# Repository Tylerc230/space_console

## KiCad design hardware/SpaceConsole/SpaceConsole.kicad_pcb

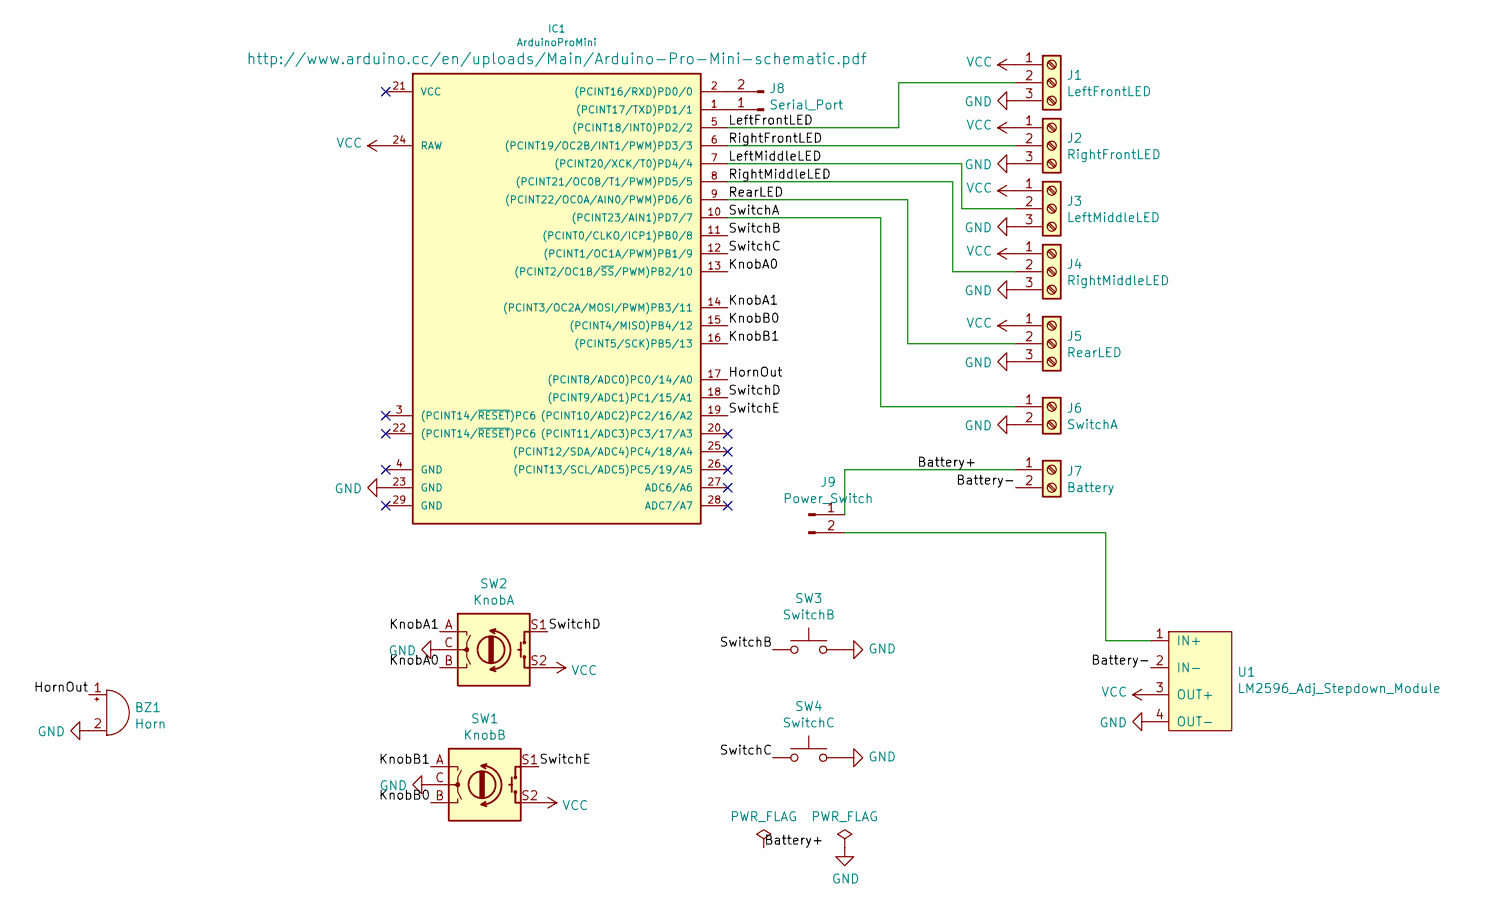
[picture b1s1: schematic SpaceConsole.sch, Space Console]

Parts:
BZ1: Horn; Buzzer_TDK_PS1240P02BT_D12.2mm_H6.5mm
IC1: ArduinoProMini; pro_mini
J1: LeftFrontLED; TerminalBlock_RND_205-00046_1x03_P5.00mm_Horizontal
J2: RightFrontLED; TerminalBlock_RND_205-00046_1x03_P5.00mm_Horizontal
J3: LeftMiddleLED; TerminalBlock_RND_205-00046_1x03_P5.00mm_Horizontal
J4: RightMiddleLED; TerminalBlock_RND_205-00046_1x03_P5.00mm_Horizontal
J5: RearLED; TerminalBlock_RND_205-00046_1x03_P5.00mm_Horizontal
J6: SwitchA; TerminalBlock_RND_205-00045_1x02_P5.00mm_Horizontal
J7: Battery; TerminalBlock_RND_205-00045_1x02_P5.00mm_Horizontal
J8: Serial_Port; PinHeader_1x02_P2.54mm_Vertical
J9: Power_Switch; PinHeader_1x02_P2.54mm_Vertical
SW1: KnobB; PinHeader_1x05_P2.54mm_Vertical
SW2: KnobA; PinHeader_1x05_P2.54mm_Vertical
SW3: SwitchB; PinHeader_1x02_P2.54mm_Vertical
SW4: SwitchC; PinHeader_1x02_P2.54mm_Vertical
U1: LM2596_Adj_Stepdown_Module

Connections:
/Battery+: J7.1, J9.1
/Battery-: J7.2, U1.2 (IN-)
/HornOut: BZ1.1 (-), IC1.17 ((PCINT8/ADC0)PC0/14/A0)
/KnobA0: IC1.13 ((PCINT2/OC1B/~SS~/PWM)PB2/10), SW2.B
/KnobA1: IC1.14 ((PCINT3/OC2A/MOSI/PWM)PB3/11), SW2.A
/KnobB0: IC1.15 ((PCINT4/MISO)PB4/12), SW1.B
/KnobB1: IC1.16 ((PCINT5/SCK)PB5/13), SW1.A
/LeftFrontLED: IC1.5 ((PCINT18/INT0)PD2/2), J1.2
/LeftMiddleLED: IC1.7 ((PCINT20/XCK/T0)PD4/4), J3.2
/RearLED: IC1.9 ((PCINT22/OC0A/AIN0/PWM)PD6/6), J5.2
/RightFrontLED: IC1.6 ((PCINT19/OC2B/INT1/PWM)PD3/3), J2.2
/RightMiddleLED: IC1.8 ((PCINT21/OC0B/T1/PWM)PD5/5), J4.2
/SwitchA: IC1.10 ((PCINT23/AIN1)PD7/7), J6.1
/SwitchB: IC1.11 ((PCINT0/CLKO/ICP1)PB0/8), SW3.1
/SwitchC: IC1.12 ((PCINT1/OC1A/PWM)PB1/9), SW4.1
/SwitchD: IC1.18 ((PCINT9/ADC1)PC1/15/A1), SW2.S1
/SwitchE: IC1.19 ((PCINT10/ADC2)PC2/16/A2), SW1.S1
GND: BZ1.2 (+), IC1.23 (GND), J1.3, J2.3, J3.3, J4.3, J5.3, J6.2, SW1.C, SW2.C, SW3.2, SW4.2, U1.4 (OUT-)
unnamed: IC1.1 ((PCINT17/TXD)PD1/1), J8.1
unnamed: IC1.2 ((PCINT16/RXD)PD0/0), J8.2
unnamed: J9.2, U1.1 (IN+)
VCC: IC1.24 (RAW), J1.1, J2.1, J3.1, J4.1, J5.1, SW1.S2, SW2.S2, U1.3 (OUT+)

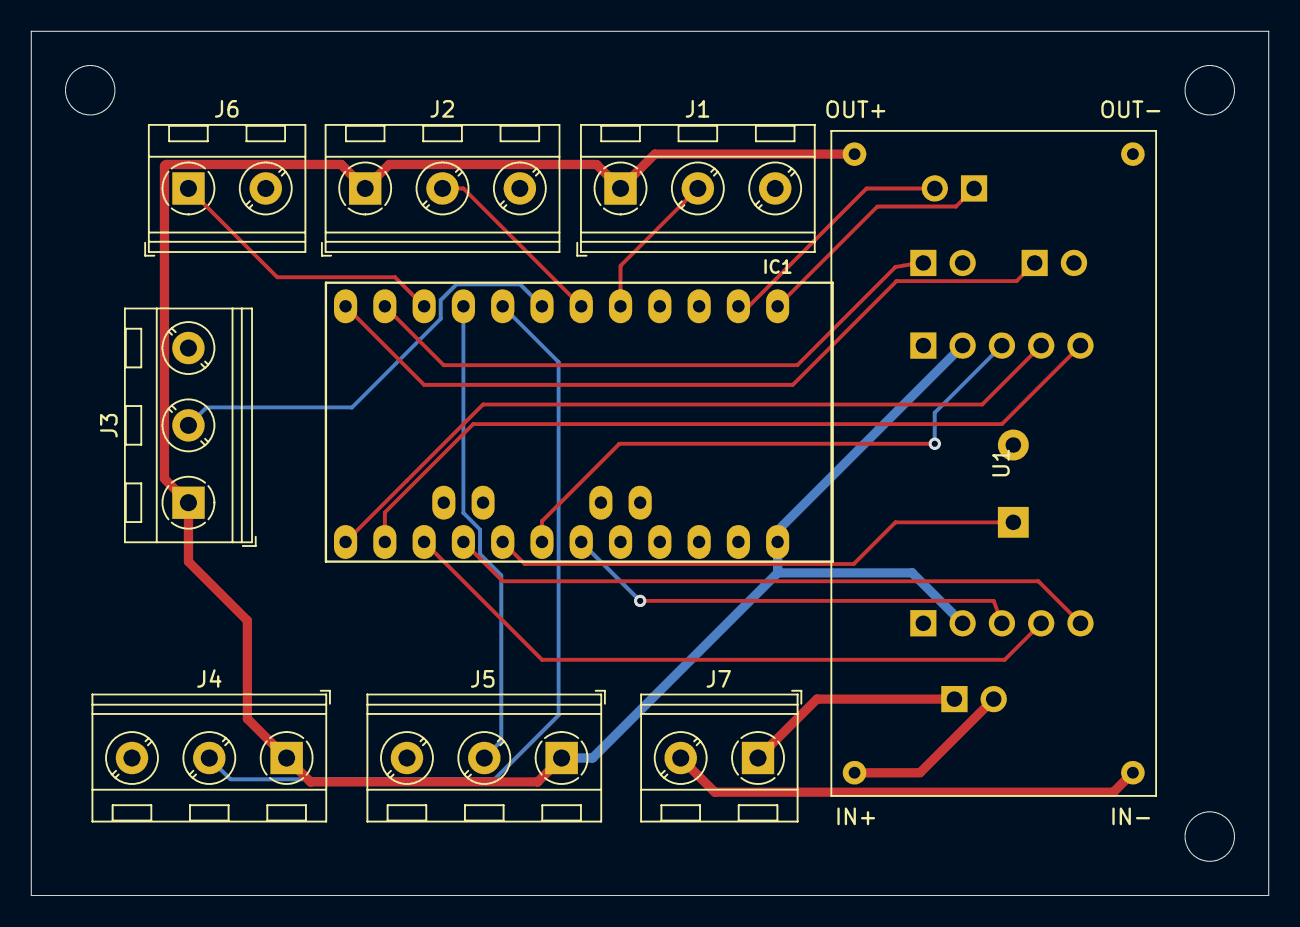
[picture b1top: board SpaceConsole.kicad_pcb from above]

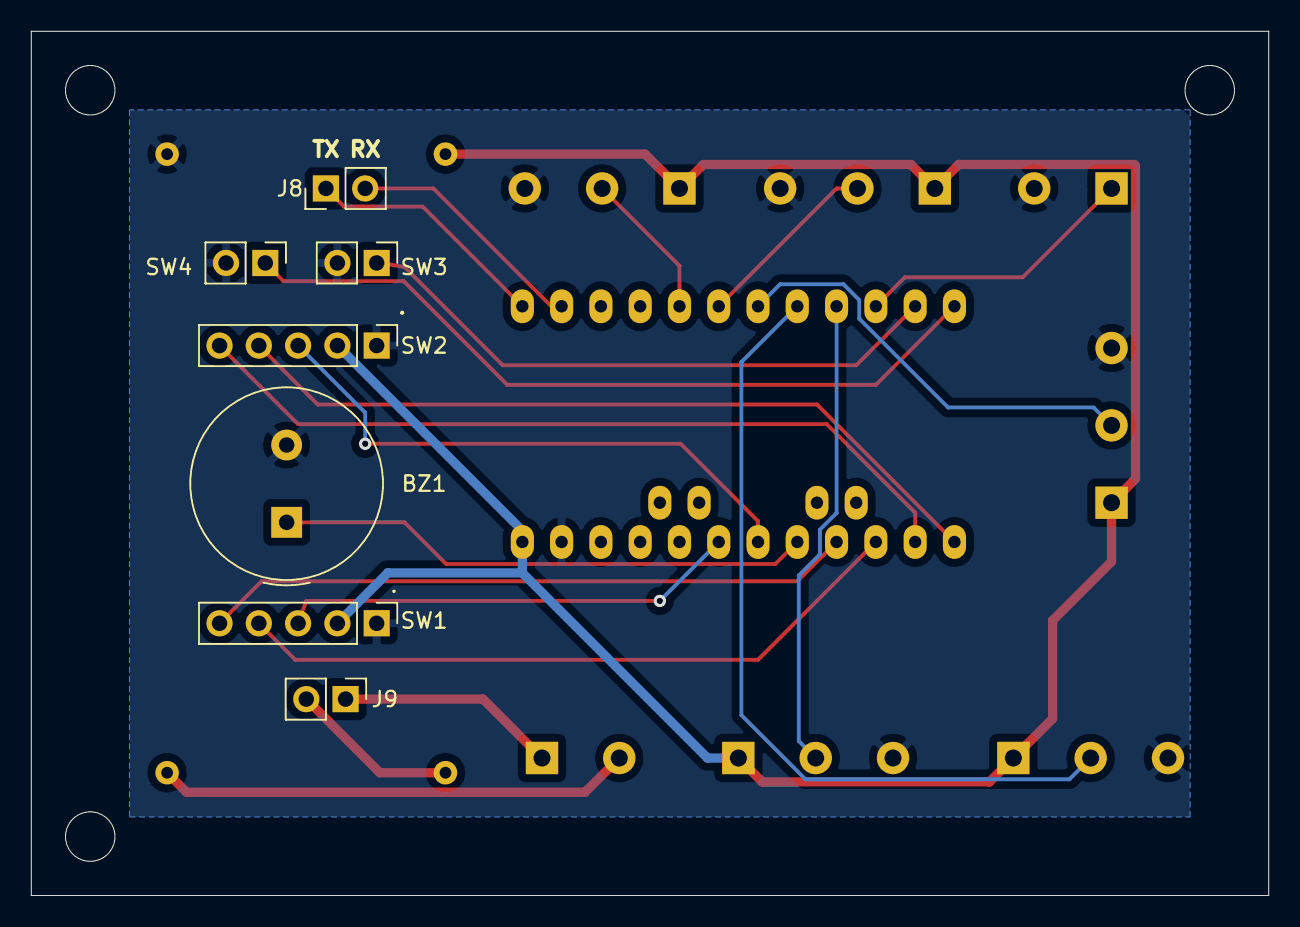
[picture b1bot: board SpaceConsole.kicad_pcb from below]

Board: 2 copper layers, 80.0 x 55.9 mm, 16 parts (7 on the bottom side), 22 nets.

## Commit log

2020-11-18 Initial commit with hardware stuff
2020-11-18 Add pro mini to schematic
2020-11-18 Label all pins
2020-11-18 Add screw terminals
2020-11-18 Add switching regulator and lib
2020-11-18 Add Know/switch headers
2020-11-18 Add footprints for all components (except Buck)
2020-11-18 Add footprint to Buck
2020-11-19 PCB layed out (no traces yet)
2020-11-19 Routing done
2020-11-19 Remove extra pins from pro
2020-11-19 Thicker power traces, add edge cutout
2020-11-19 Add power switch
2020-11-22 Add knobs and switches to schematic
2020-11-22 Add routing for knobs and switches
2020-11-22 Move knobs and switches to back, readd drill holes
2020-11-22 Update silk screen
2020-11-22 Gerber output settings
2020-11-25 docker file with ROS installed
2021-09-15 Add firmware project
2021-10-27 Firmware cmake file update
2021-10-27 rpi + docker + ros
2021-10-27 Add rust firmware crate
2021-11-02 Move timer code to its own module
2021-11-02 Create program/testprogram in library crate
2021-11-03 Allow host unit test
    I have enabled unit testing for functional code by placing all avr
    dependent code in an 'avr' sub package. I can run cargo test in the
    workspace root and it will build and run locally. I can run cargo build
    in the avr folder and it will build for arduino.
2021-11-03 Remove unused files
2021-11-04 Test compiling
2021-11-04 1D pixel buffer test passing
2021-11-05 Create pixel buffer object to hold pixels
2021-11-05 Flatten 2d array
2021-11-05 Hook up program running to actual code
2021-11-07 Rename some values
2021-11-09 Multiple strips compiling
2021-11-09 Handle multiple led strips
2021-11-09 Runner owns the buffer now
2021-11-09 All 5 strips added, not working
2021-11-09 4 out of 5 leds flashing
    Unrolling for loop and moving buffer out of runner and it works. Pin 2
    still not working.
2021-11-09 Unit tests passing
2021-11-09 Add global serial
2021-11-11 Remove warning about profiles
2021-11-12 Put programs in enum for now to avoid dyn
2021-11-17 Move led code to own file
2021-11-20 Read both knobs
2021-11-20 Move input drive to its own module
2021-11-22 Fix warnings
2021-12-01 Use interrupts for inputs
2021-12-01 Hard code pins in input, update in ISR
2021-12-02 Fix left and right rotary, print pin values
2021-12-02 Add mutex
2021-12-03 Use Arduino-CMake-Toolchain
2021-12-03 Create source folder
2021-12-03 Fix crash in rain program
